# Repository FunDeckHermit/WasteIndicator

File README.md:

# Waste Indicator
Scripts that modify Tasmota to interact with the Ximmio waste API. The color of an LED is set the day before a pickup date. It should also be easy to integrate into Home Assistant. 

## What it does:
* Sets the color of an RGB LED on the day before a pickup date
* Hides the RGB LED controls from Tasmota's main page
* Adds a form to set home adres
* Queries Ximmio's API to get the uniqueID of the adres
* Queries pickup dates every 12 hours
* Add a button to turn the LED off
* Save configuration during reset
* Reset configuration when holding button 8 seconds

## To-do
* Integrate into Home Assistant
* Don't use the companyCode of my local waste collector
* Test with a Tasmota compatible RGB light bulb
* Blink LED on first boot

# How to flash
Use a Webserial based ESP32 flasher or use ESPtool from the command line to flash the PCB.
First solder the "Boot" jumper, then hold the button to get the ESP32 into boot mode.

`esptool --port /dev/ttyACM0 erase_flash`   
`esptool --port /dev/ttyACM0 write_flash 0x0 tasmota32s2.factory.bin`

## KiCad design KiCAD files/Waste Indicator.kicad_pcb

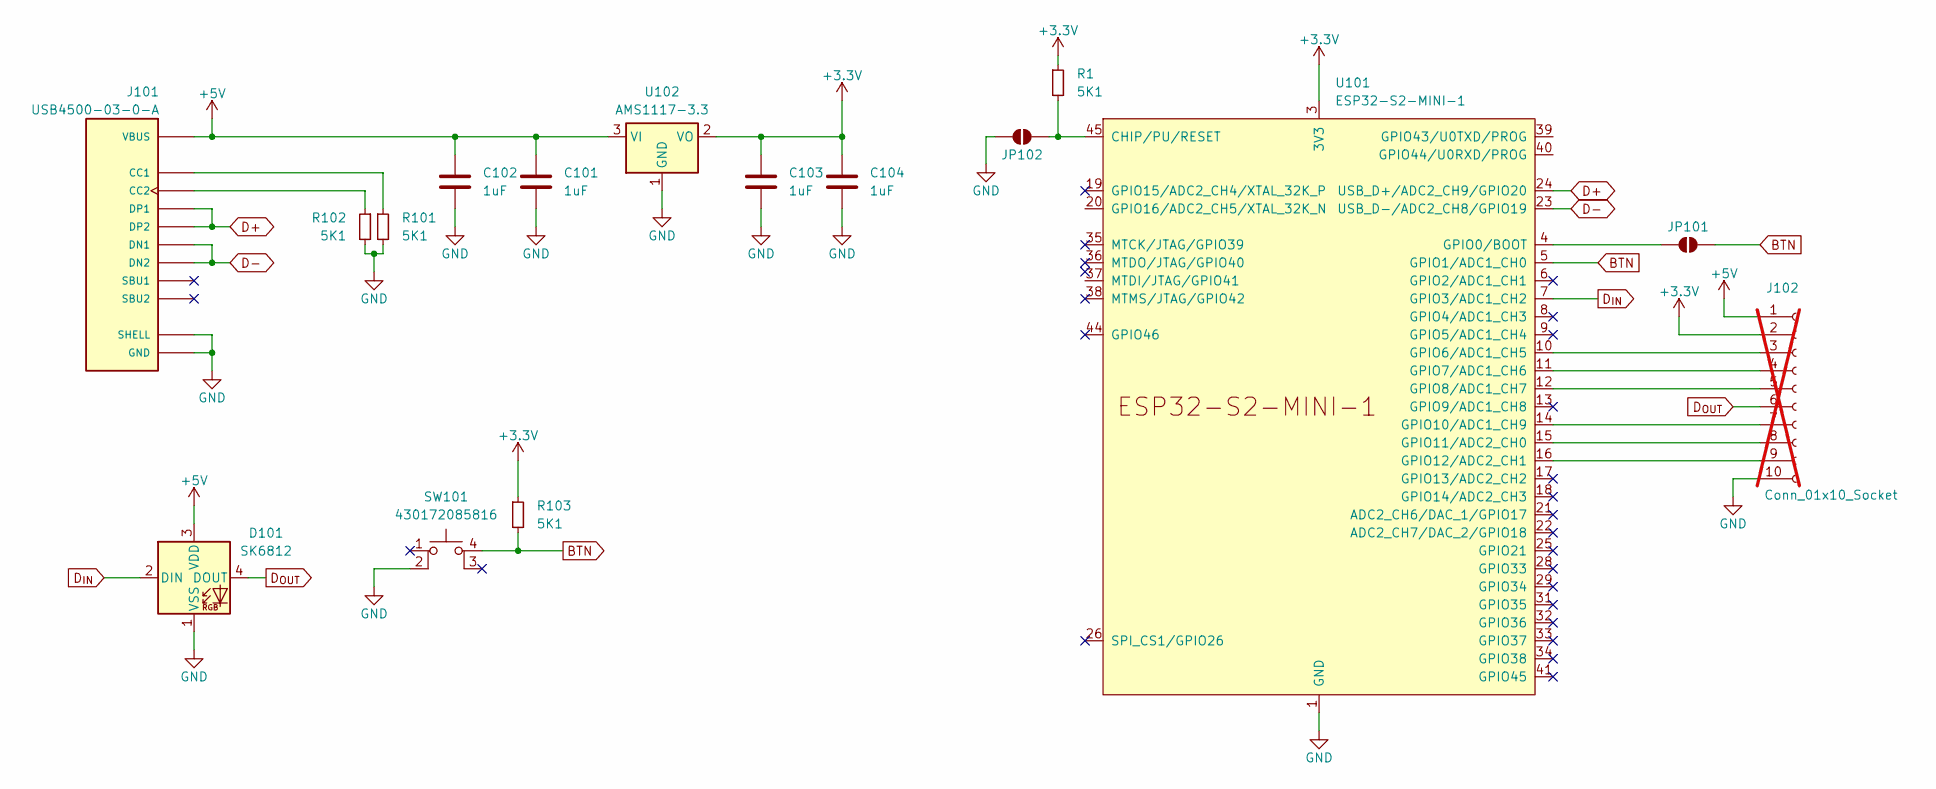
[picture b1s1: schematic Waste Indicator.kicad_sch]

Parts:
C101, C102, C103, C104: 1uF; C_0805_2012Metric
D101: SK6812; LED_SK6812_PLCC4_5.0x5.0mm_P3.2mm
J101: USB4500-03-0-A; USB_C_Receptacle_USB4500-03-0-A
J102: Conn_01x10_Socket; PinHeader_1x10_P2.54mm_Vertical; not fitted
JP101, JP102: SolderJumper_2_Open; SolderJumper-2_P1.3mm_Open_TrianglePad1.0x1.5mm
R1, R101, R102, R103: 5K1; R_0603_1608Metric
SW101: 430172085816; btn_momentary_430172085816
U101: ESP32-S2-MINI-1
U102: AMS1117-3.3; SOT-223-3_TabPin2

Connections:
+3.3V: C103.1, C104.1, J102.2, R1.1, R103.1, U101.3 (3V3), U102.2 (VO)
+5V: C101.1, C102.1, D101.3 (VDD), J101.A4 (VBUS), J101.A9 (VBUS), J101.B4 (VBUS), J101.B9 (VBUS), J102.1, U102.3 (VI)
BTN: JP101.2 (B), R103.2, SW101.4, U101.5 (GPIO1/ADC1_CH0)
D+: J101.A6 (DP1), J101.B6 (DP2), U101.24 (USB_D+/ADC2_CH9/GPIO20)
D-: J101.A7 (DN1), J101.B7 (DN2), U101.23 (USB_D-/ADC2_CH8/GPIO19)
D_{IN}: D101.2 (DIN), U101.7 (GPIO3/ADC1_CH2)
D_{OUT}: D101.4 (DOUT), J102.6
GND: C101.2, C102.2, C103.2, C104.2, D101.1 (VSS), J101.A1 (GND), J101.A12 (GND), J101.B1 (GND), J101.B12 (GND), J101.S1 (SHELL), J102.10, JP102.2 (B), R101.2, R102.2, SW101.2, U101.1 (GND), U101.2 (GND), U101.30 (GND), U101.42 (GND), U101.43 (GND), U101.46 (GND), U101.47 (GND), U101.48 (GND), U101.49 (GND), U101.50 (GND), U101.51 (GND), U101.52 (GND), U101.53 (GND), U101.54 (GND), U101.55 (GND), U101.56 (GND), U101.57 (GND), U101.58 (GND), U101.59 (GND), U101.60 (GND), U101.61 (GND), U101.62 (GND), U101.63 (GND), U101.64 (GND), U101.65 (GND), U102.1 (GND)
unnamed: J101.A5 (CC1), R101.1
unnamed: J101.B5 (CC2), R102.1
unnamed: J102.3, U101.10 (GPIO6/ADC1_CH5)
unnamed: J102.4, U101.11 (GPIO7/ADC1_CH6)
unnamed: J102.5, U101.12 (GPIO8/ADC1_CH7)
unnamed: J102.7, U101.14 (GPIO10/ADC1_CH9)
unnamed: J102.8, U101.15 (GPIO11/ADC2_CH0)
unnamed: J102.9, U101.16 (GPIO12/ADC2_CH1)
unnamed: JP101.1 (A), U101.4 (GPIO0/BOOT)
unnamed: JP102.1 (A), R1.2, U101.45 (CHIP/PU/RESET)

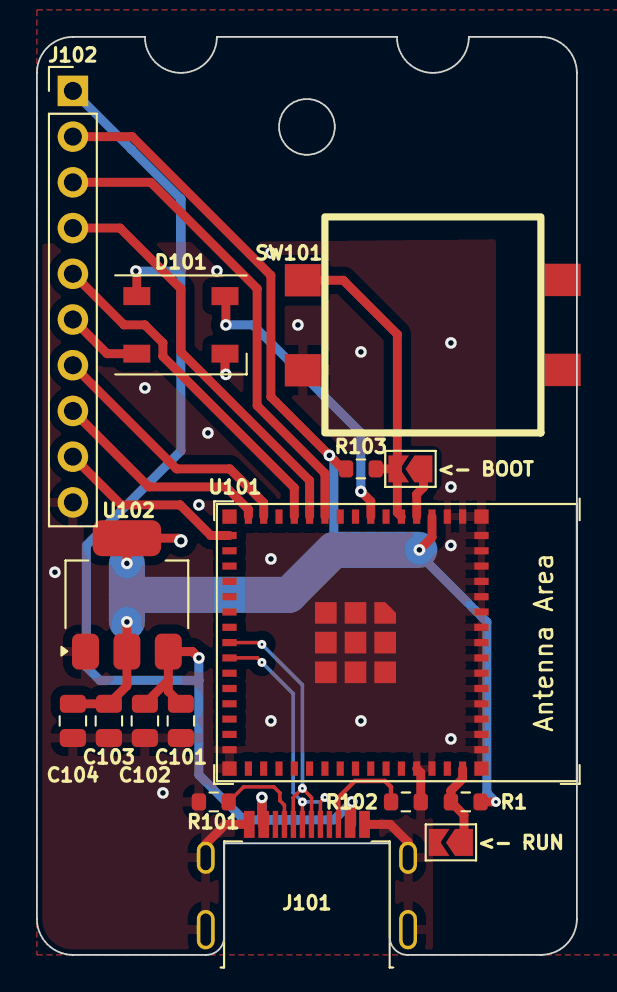
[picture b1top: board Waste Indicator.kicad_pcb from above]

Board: 2 copper layers, 30.0 x 51.0 mm, 16 parts (0 on the bottom side), 18 nets.

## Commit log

2024-06-30 Initial push for scripts
2024-07-19 Added KiCAD and OnShape files
2024-08-15 Streamlined compilation
2024-08-15 Added Compilation file
2024-08-15 Minor bug fixed after reset
2024-08-15 Fixed PCB to V1.0
2024-08-15 Fixed a big affecting brightness
